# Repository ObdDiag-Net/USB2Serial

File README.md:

PIC16F1454 USB to Serial Converter Firmware
==========================================

See http://www.obddiag.net/usb-2-serial.html project page for details.

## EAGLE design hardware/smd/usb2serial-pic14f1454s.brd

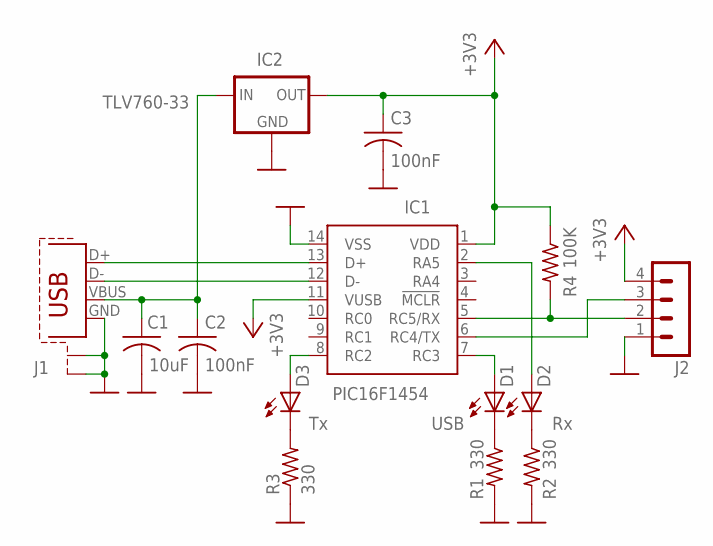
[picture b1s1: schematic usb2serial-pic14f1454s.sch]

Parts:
C1: 10uF; C0805
C2, C3: 100nF; C0805
D1, D2, D3: Green; CHIPLED_0805
IC1: PIC16F1454; SOIC-14
IC2: TLV760-33; SOT23
J1: USB-SHIELD-A-H1; USB-A-H1
J2: J2; MA04-1
R1, R2, R3: 330; R0805
R4: 100K; R0805

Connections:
+3V3: C3.1, IC1.1 (VDD), IC1.11 (VUSB), IC2.1 (OUT), J2.4, R4.1
GND: C1.2, C2.2, C3.2, IC1.14 (VSS), IC2.3 (GND), J1.GND, J1.GND2 (S1), J1.GND3 (S2), J2.1, R1.2, R2.2, R3.1
unnamed: D3.C, R3.2
unnamed: D1.C, R1.1
unnamed: IC1.12 (D-), J1.D-
unnamed: IC1.13 (D+), J1.D+
unnamed: D2.C, R2.1
unnamed: IC1.5 (RC5/RX), J2.2, R4.2
unnamed: C1.1, C2.1, IC2.2 (IN), J1.VBUS
unnamed: D1.A, IC1.7 (RC3)
RA5: D2.A, IC1.2 (RA5)
RC2: D3.A, IC1.8 (RC2)
TX1: IC1.6 (RC4/TX), J2.3

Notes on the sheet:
USB

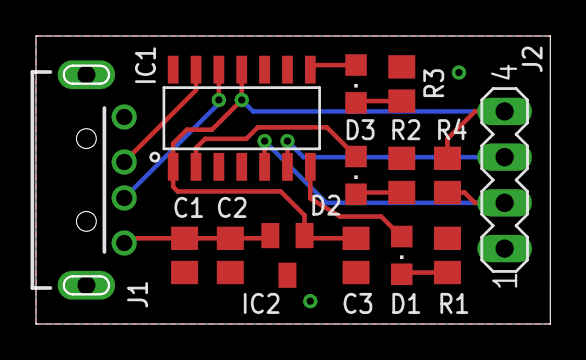
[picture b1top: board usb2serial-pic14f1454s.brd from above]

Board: 2 copper layers, 28.4 x 15.9 mm, 14 parts (0 on the bottom side), 13 nets.

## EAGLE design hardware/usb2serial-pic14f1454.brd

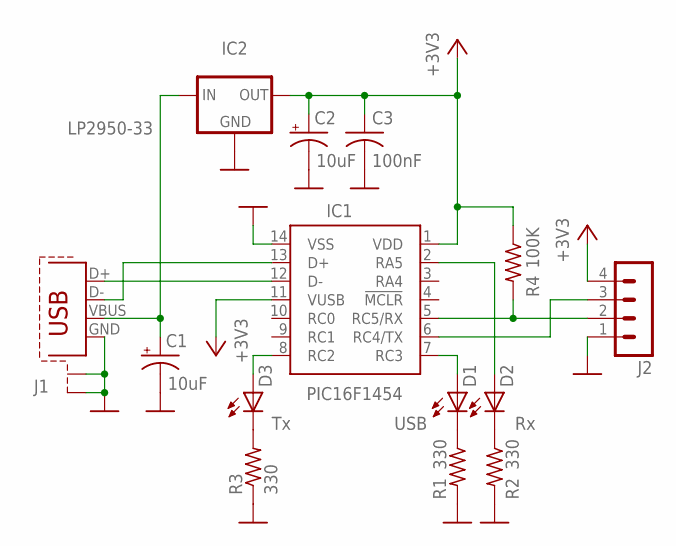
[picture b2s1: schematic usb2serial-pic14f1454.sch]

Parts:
C1, C2: 10uF; E2-4
C3: 100nF; C050-025X075
D1, D2, D3: LED5MM
IC1: PIC16F1454; DIL14
IC2: LP2950-33; 78LXX
J1: USB-SHIELD-A-H; USB-A-H
J2: J2; MA04-1
R1, R2, R3: 330; 0207/10
R4: 100K; 0207/10

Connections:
+3V3: C2.+, C3.1, IC1.1 (VDD), IC1.11 (VUSB), IC2.OUT, J2.4, R4.1
GND: C1.-, C2.-, C3.2, IC1.14 (VSS), IC2.GND, J1.GND, J1.GND2 (S1), J1.GND3 (S2), J2.1, R1.2, R2.2, R3.1
unnamed: IC1.13 (D+), J1.D-
unnamed: IC1.12 (D-), J1.D+
unnamed: IC1.5 (RC5/RX), J2.2, R4.2
unnamed: D3.K (C), R3.2
unnamed: D2.K (C), R2.1
unnamed: C1.+, IC2.IN, J1.VBUS
unnamed: D1.A, IC1.7 (RC3)
unnamed: D1.K (C), R1.1
RA5: D2.A, IC1.2 (RA5)
RC2: D3.A, IC1.8 (RC2)
TX: IC1.6 (RC4/TX), J2.3

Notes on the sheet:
USB

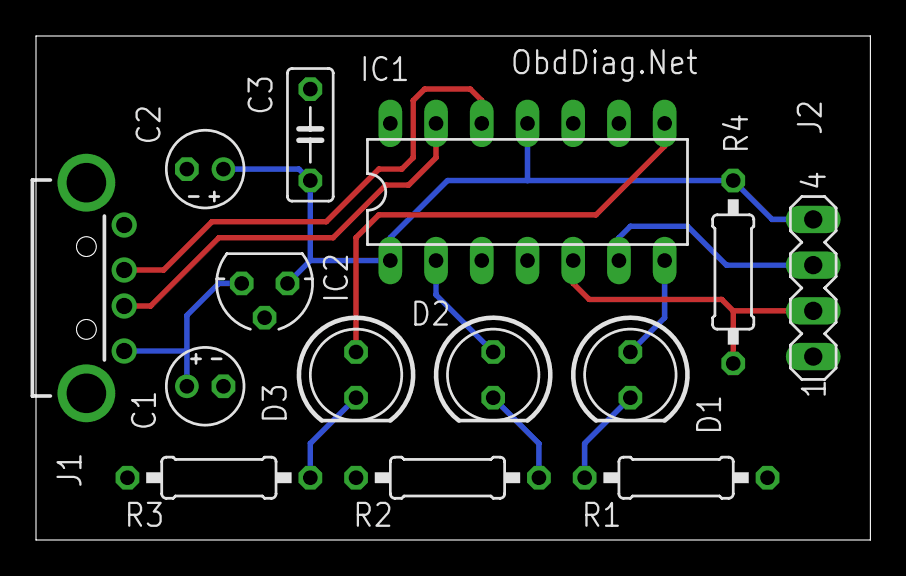
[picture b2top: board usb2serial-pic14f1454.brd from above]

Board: 2 copper layers, 46.4 x 28.0 mm, 14 parts (0 on the bottom side), 13 nets.

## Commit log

2020-06-09 Cleanup
2020-06-10 Addded SMD version
2020-06-14 Fixed D+/D- bug
2020-06-16 Minor adjustments
